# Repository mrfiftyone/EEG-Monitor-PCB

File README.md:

# EEG Monitor Prototype

An open-source brainwave monitor prototype built with KiCad.

## Hardware Overview
* **Microcontroller:** ESP32-WROOM-32E (Wi-Fi/Bluetooth enabled)
* **ADC:** Texas Instruments ADS1299 (Low-Noise, 8-channel, 24-bit analog-to-digital converter)

## Manufacturing
The Gerber files required for PCB fabrication (copper, silkscreen, solder mask, edge cuts, and drill files) are bundled in the release section or located in the `EEG_Gerbers` folder.

## How to Open
To view or modify this project, you will need [KiCad](https://www.kicad.org/). Open the `EEG-Monitor.kicad_pro` file in the KiCad project manager.

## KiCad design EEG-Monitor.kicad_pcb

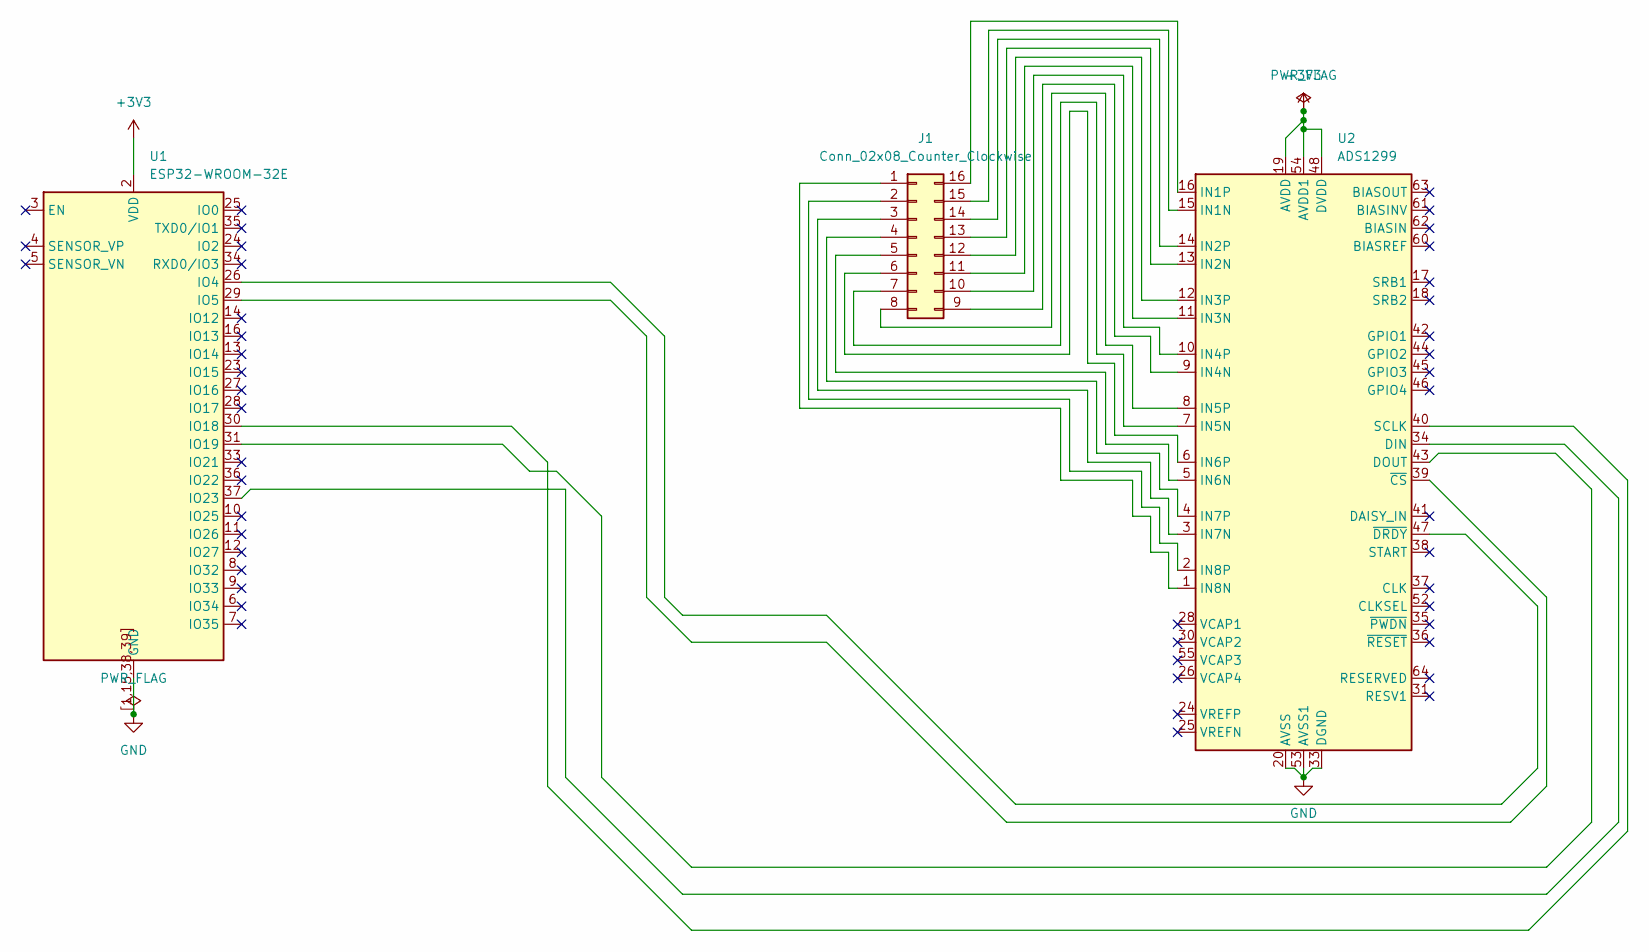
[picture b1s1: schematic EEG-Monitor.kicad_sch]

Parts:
J1: Conn_02x08_Counter_Clockwise; PinSocket_2x08_P2.54mm_Vertical
U1: ESP32-WROOM-32E; ESP32-WROOM-32
U2: ADS1299; TQFP-64_10x10mm_P0.5mm

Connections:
+3V3: U1.2 (VDD), U2.19 (AVDD), U2.21 (AVDD), U2.22 (AVDD), U2.48 (DVDD), U2.50 (DVDD), U2.54 (AVDD1), U2.56 (AVDD), U2.59 (AVDD)
GND: U1.1 (GND), U1.15 (GND), U1.38 (GND), U1.39 (GND), U1.[1,15,38,39] (GND), U2.20 (AVSS), U2.23 (AVSS), U2.32 (AVSS), U2.33 (DGND), U2.49 (DGND), U2.51 (DGND), U2.53 (AVSS1), U2.57 (AVSS), U2.58 (AVSS)
unnamed: J1.1, U2.1 (IN8N)
unnamed: J1.2, U2.2 (IN8P)
unnamed: J1.3, U2.3 (IN7N)
unnamed: J1.4, U2.4 (IN7P)
unnamed: J1.5, U2.5 (IN6N)
unnamed: J1.6, U2.6 (IN6P)
unnamed: J1.7, U2.7 (IN5N)
unnamed: J1.8, U2.8 (IN5P)
unnamed: J1.9, U2.9 (IN4N)
unnamed: J1.10, U2.10 (IN4P)
unnamed: J1.11, U2.11 (IN3N)
unnamed: J1.12, U2.12 (IN3P)
unnamed: J1.13, U2.13 (IN2N)
unnamed: J1.14, U2.14 (IN2P)
unnamed: J1.15, U2.15 (IN1N)
unnamed: J1.16, U2.16 (IN1P)
unnamed: U1.26 (IO4), U2.47 (~DRDY)
unnamed: U1.29 (IO5), U2.39 (~CS)
unnamed: U1.30 (IO18), U2.40 (SCLK)
unnamed: U1.31 (IO19), U2.43 (DOUT)
unnamed: U1.37 (IO23), U2.34 (DIN)

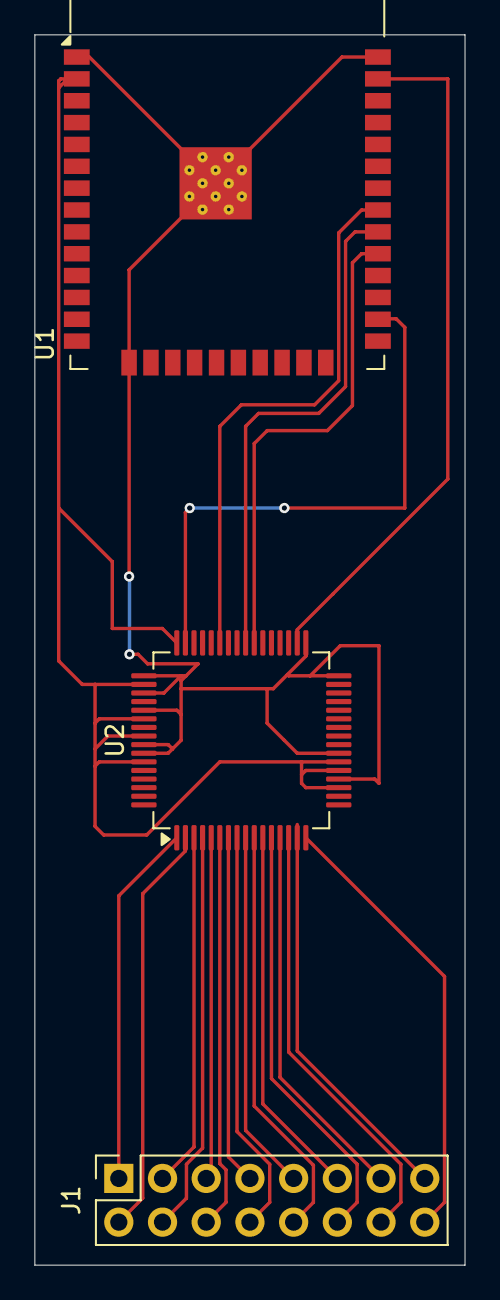
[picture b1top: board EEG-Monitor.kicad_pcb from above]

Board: 2 copper layers, 25.0 x 71.5 mm, 3 parts (0 on the bottom side), 23 nets.
